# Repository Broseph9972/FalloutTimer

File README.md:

# FalloutTimer

---
The FalloutTimer™ is a simple timer that uses an RTC, A pi Pico, Some buttons, and some cheap 7 segment displays to tell you how much time is left in Hack club fallout!
(Can be used for other things as well)
# Assembly

Assembly is relatively simple, Solder the pico, buttons, caps, and RTC, into the spots they appear on the pcb/zine. look at the zine for info about how to solder the 7-seg display, then flash the firmware by holding down the boot button on the pico while plugging it in. then compile the code and drop the uf2 into the pico's flash. it should reboot and work. Thats really all you need.
--- 
# Usage
Simply set the time via the buttons on the bottom. left button controls days and hrs, left controls mins. seconds are always set to zero for simplicity. if you click the left button it will change hrs, if u hold it down, then it will change days. Thats basically it.
---
## Why?
I decided to make it because i need more time for fallout and it seemed like a simple project i could do to increase my amount of approved hours. also it looks cool as wall deco. ill probably bring it to fallout to show the amount of time left
It displays the time left in fallout with Day,Hour,Minutes,Seconds, similar to the fallout website. also i might get it to check streaks too maybe? <- no wifi so probably not. u would need a pico w aswell.

|Name                       |Price|Link                                                                                                                                                                                                                                                                                                                                                                                                                 |Quantity|Notes                                              |
|---------------------------|-----|---------------------------------------------------------------------------------------------------------------------------------------------------------------------------------------------------------------------------------------------------------------------------------------------------------------------------------------------------------------------------------------------------------------------|--------|---------------------------------------------------|
|7 Segment display          |$2.77|https://www.aliexpress.us/item/2255801097197605.html?algo_exp_id=59cf0bf3-654c-4eec-9474-7ea4b6c6c45e-1&pdp_ext_f=%7B%22order%22%3A%22464%22%2C%22eval%22%3A%221%22%2C%22fromPage%22%3A%22search%22%7D&utparam-url=scene%3Asearch%7Cquery_from%3A%7Cx_object_id%3A4001283512357%7C_p_origin_prod%3A                                                                                                                  |1       |Comes with 8 digits built in. built for 0.56"      |
|Pi Pico                    |$0.99|https://www.aliexpress.us/item/3256806652932348.html?algo_exp_id=9f39b4b5-7e06-4d57-8f12-5c0bc45dbe9d-2&pdp_ext_f=%7B%22order%22%3A%221158%22%2C%22eval%22%3A%221%22%2C%22fromPage%22%3A%22search%22%7D&utparam-url=scene%3Asearch%7Cquery_from%3A%7Cx_object_id%3A1005006839247100%7C_p_origin_prod%3A                                                                                                              |1       |Lots of fakes, shouldnt matter. get usb-c if u want|
|PCB                        |$7.12|JLCPCB.com                                                                                                                                                                                                                                                                                                                                                                                                           |1       |Upload the gerber from the repo.                   |
|DS3231M RTC                |$1.39|https://www.aliexpress.us/item/3256807808551126.html?aem_p4p_detail=202605301909028322147092268240002707967&algo_exp_id=f0b65990-3f51-4963-9e20-ac16821638a2-3&pdp_ext_f=%7B%22order%22%3A%22336%22%2C%22eval%22%3A%221%22%2C%22fromPage%22%3A%22search%22%7D&utparam-url=scene%3Asearch%7Cquery_from%3A%7Cx_object_id%3A1005007994865878%7C_p_origin_prod%3A&search_p4p_id=202605301909028322147092268240002707967_1|1       |so u dont gotta reset the clock everytime          |
|100nF Cap                  |$1.58|https://www.aliexpress.us/item/3256802327709422.html?algo_exp_id=1eb7f3bd-4212-4056-b126-b8978d5f2388-0&pdp_ext_f=%7B%22order%22%3A%22251%22%2C%22eval%22%3A%221%22%2C%22fromPage%22%3A%22search%22%7D&utparam-url=scene%3Asearch%7Cquery_from%3A%7Cx_object_id%3A1005002514024174%7C_p_origin_prod%3A                                                                                                               |1       |Technically optional, but idk                      |
|Pushbuttons                |$0.99|https://www.aliexpress.us/item/2251832687083572.html?algo_exp_id=f1680402-12bf-4261-921e-e1ba355f5f7b-6&pdp_ext_f=%7B%22order%22%3A%22366%22%2C%22eval%22%3A%221%22%2C%22fromPage%22%3A%22search%22%7D&utparam-url=scene%3Asearch%7Cquery_from%3A%7Cx_object_id%3A32873398324%7C_p_origin_prod%3A                                                                                                                    |2       |For input                                          |
|3d printed parts (optional)|$0   |N/A                                                                                                                                                                                                                                                                                                                                                                                                                  |1       |Not needed but just there ig                       |

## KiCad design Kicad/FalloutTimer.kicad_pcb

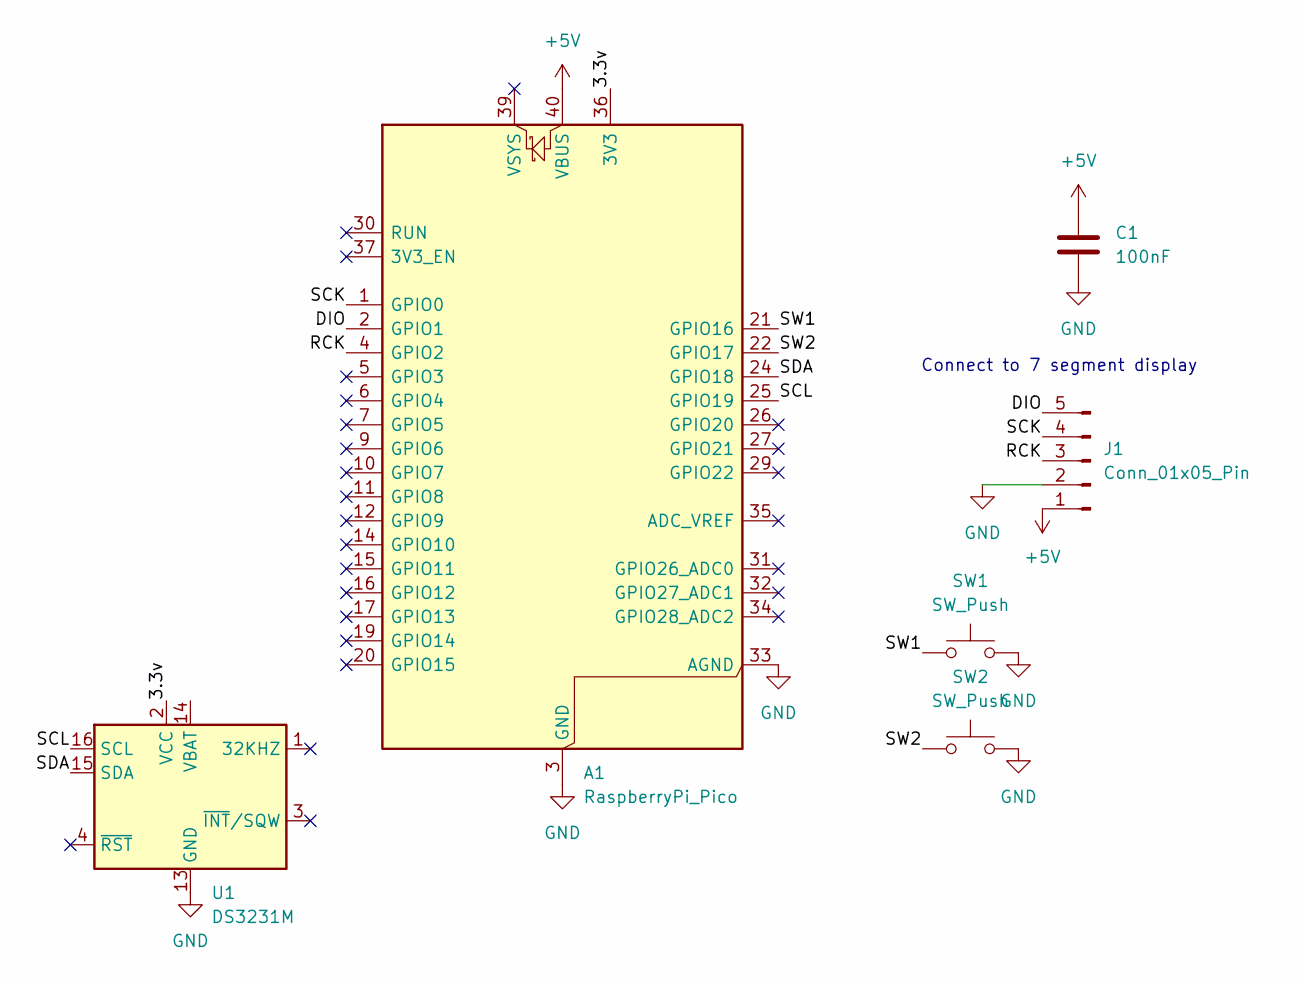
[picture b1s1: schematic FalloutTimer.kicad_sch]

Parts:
A1: RaspberryPi_Pico; RaspberryPi_Pico_Common_Unspecified
C1: 100nF; C_Disc_D5.0mm_W2.5mm_P5.00mm
J1: Conn_01x05_Pin; PinHeader_1x05_P2.54mm_Vertical
SW1, SW2: SW_Push; SW_PUSH_6mm
U1: DS3231M; SOIC-16W_7.5x10.3mm_P1.27mm

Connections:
+5V: A1.40 (VBUS), C1.1, J1.1
/3.3v: A1.36 (3V3), U1.2 (VCC)
/DIO: A1.2 (GPIO1), J1.5
/RCK: A1.4 (GPIO2), J1.3
/SCK: A1.1 (GPIO0), J1.4
/SCL: A1.25 (GPIO19), U1.16 (SCL)
/SDA: A1.24 (GPIO18), U1.15 (SDA)
/SW1: A1.21 (GPIO16), SW1.1
/SW2: A1.22 (GPIO17), SW2.1
GND: A1.3 (GND), A1.8 (GND), A1.13 (GND), A1.18 (GND), A1.23 (GND), A1.28 (GND), A1.33 (AGND), A1.38 (GND), C1.2, J1.2, SW1.2, SW2.2, U1.5 (GND), U1.6 (GND), U1.7 (GND), U1.8 (GND), U1.9 (GND), U1.10 (GND), U1.11 (GND), U1.12 (GND), U1.13 (GND)

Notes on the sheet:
Connect to 7 segment display

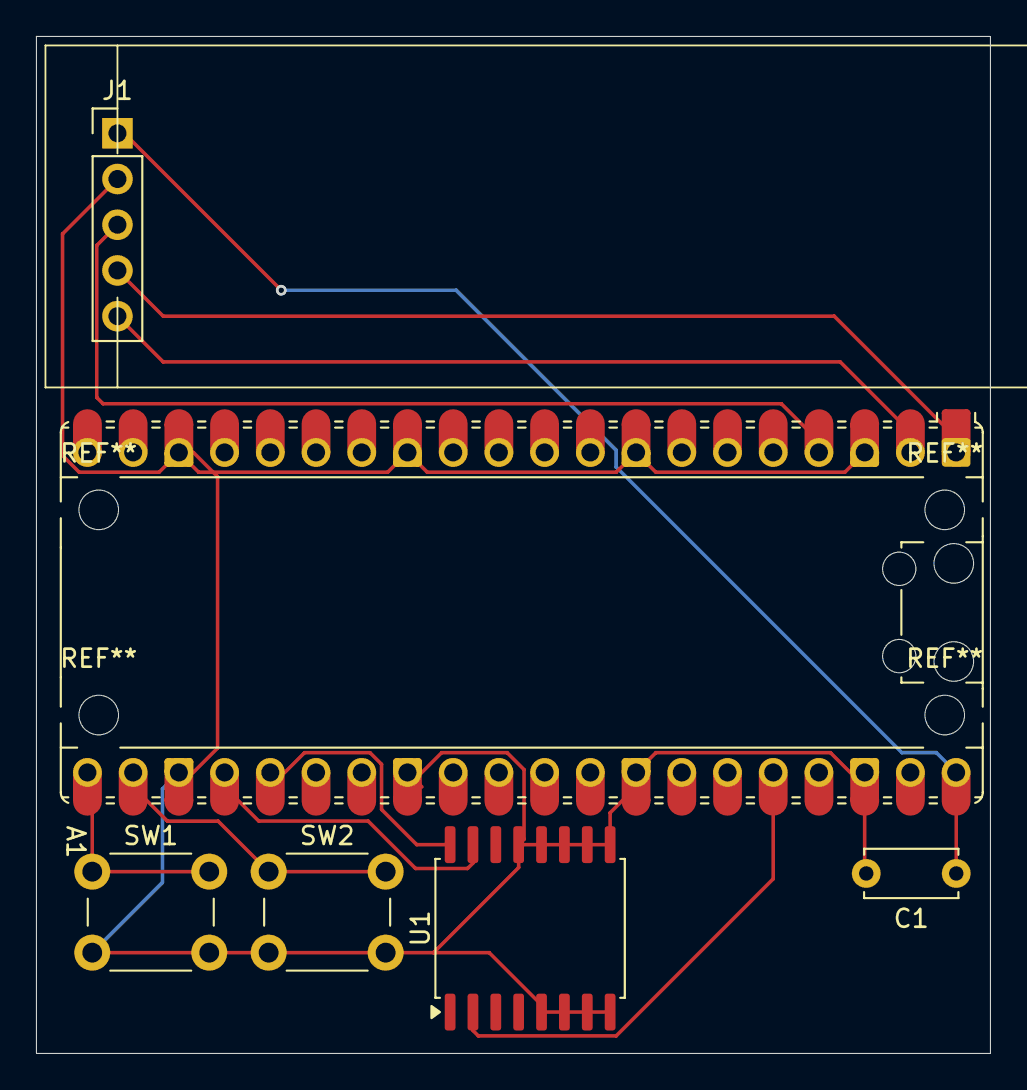
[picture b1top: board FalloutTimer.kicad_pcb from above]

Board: 2 copper layers, 53.0 x 56.5 mm, 6 parts (0 on the bottom side), 10 nets.

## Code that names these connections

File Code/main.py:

import board
import busio
import time
import digitalio
from adafruit_ds3231 import DS3231

# I2C for RTC (SDA=GPIO18, SCL=GPIO19)
i2c = busio.I2C(scl=board.GP19, sda=board.GP18)
rtc = DS3231(i2c)

# 74HC595 shift registers for 8 7-segment displays
# SCK=GPIO0 (clock), DIO=GPIO1 (data), RCK=GPIO2 (latch)
sck = digitalio.DigitalInOut(board.GP0)
sck.direction = digitalio.Direction.OUTPUT

dio = digitalio.DigitalInOut(board.GP1)
dio.direction = digitalio.Direction.OUTPUT

rck = digitalio.DigitalInOut(board.GP2)
rck.direction = digitalio.Direction.OUTPUT

# 7-segment display patterns (common cathode, DP on bit 7)
SEGMENTS = {
    0: 0b00111111,  # 0
    1: 0b00000110,  # 1
    2: 0b01011011,  # 2
    3: 0b01001111,  # 3
    4: 0b01100110,  # 4
    5: 0b01101101,  # 5
    6: 0b01111101,  # 6
    7: 0b00000111,  # 7
    8: 0b01111111,  # 8
    9: 0b01101111,  # 9
    10: 0b00000000  # blank
}

# Pushbuttons (GPIO16 and GPIO17, pulled to GND)
button_left = digitalio.DigitalInOut(board.GP16)
button_left.direction = digitalio.Direction.INPUT
button_left.pull = digitalio.Pull.UP

button_right = digitalio.DigitalInOut(board.GP17)
button_right.direction = digitalio.Direction.INPUT
button_right.pull = digitalio.Pull.UP

# Timer state (in seconds)
time_remaining = 0
setting_mode = False
blink_state = False
blink_time = 0
display_buffer = [10, 10, 10, 10, 10, 10, 10, 10]

def shift_out_byte(byte):
    """Shift out 8 bits to 74HC595"""
    for i in range(8):
        dio.value = (byte >> (7 - i)) & 1
        time.sleep(0.00005)
        sck.value = 1
        time.sleep(0.00005)
        sck.value = 0

def latch():
    """Latch data into output registers"""
    rck.value = 1
    time.sleep(0.0001)
    rck.value = 0

def shift_out_bytes(bytes_list):
    """Shift out multiple bytes (for chaining 74HC595s)"""
    for byte in reversed(bytes_list):  # Reverse for correct bit order
        shift_out_byte(byte)
    latch()

def seconds_to_display(seconds):
    """Convert seconds to day:hour:minute:second format"""
    days = seconds // 86400
    hours = (seconds % 86400) // 3600
    minutes = (seconds % 3600) // 60
    secs = seconds % 60
    return days, hours, minutes, secs

def update_display(days, hours, minutes, secs):
    """Update display buffer with DD:HH:MM:SS"""
    global display_buffer
    display_buffer = [
        days // 10,
        days % 10,
        hours // 10,
        hours % 10,
        minutes // 10,
        minutes % 10,
        secs // 10,
        secs % 10
    ]

def render_display():
    """Send display buffer to 74HC595s"""
    segments = [SEGMENTS.get(d, SEGMENTS[10]) for d in display_buffer]
    shift_out_bytes(segments)

def display_blink():
    """Blink display when timer reaches 0"""
    global blink_state, blink_time
    current_time = time.monotonic()
    if current_time - blink_time > 0.5:
        blink_state = not blink_state
        blink_time = current_time
        if blink_state:
            display_buffer[:] = [10] * 8
        else:
            update_display(0, 0, 0, 0)
    render_display()

def check_both_buttons_held():
    """Check if both buttons are held down"""
    return not button_left.value and not button_right.value

# Main loop
last_second_update = time.monotonic()
left_pressed = False
right_pressed = False
button_held_time = 0

while True:
    current_time = time.monotonic()
    both_held = check_both_buttons_held()
    
    # Enter/exit setting mode
    if both_held and not setting_mode:
        setting_mode = True
        button_held_time = current_time
    elif setting_mode and not both_held:
        setting_mode = False
    
    if setting_mode:
        # In setting mode - adjust time with button presses
        if not button_left.value and not left_pressed:
            # Left button: add hour
            left_pressed = True
            time_remaining = min(time_remaining + 3600, 9999999)
            print(f"Timer: {time_remaining}s (+1h)")
            time.sleep(0.1)
        elif button_left.value:
            left_pressed = False
        
        if not button_right.value and not right_pressed:
            # Right button: add minute (reset seconds), or add day if held
            right_pressed = True
            hold_duration = current_time - button_held_time
            if hold_duration > 1.0:
                # Long hold: add day
                time_remaining = min(time_remaining + 86400, 9999999)
                print(f"Timer: {time_remaining}s (+1d)")
            else:
                # Short press: add minute, reset seconds
                time_remaining = (time_remaining // 60 + 1) * 60
                time_remaining = min(time_remaining, 9999999)
                print(f"Timer: {time_remaining}s (+1m)")
            time.sleep(0.1)
        elif button_right.value:
            right_pressed = False
        
        # Display time being set
        days, hours, minutes, secs = seconds_to_display(time_remaining)
        update_display(days, hours, minutes, secs)
        render_display()
    
    else:
        # Normal countdown mode
        if current_time - last_second_update >= 1.0:
            if time_remaining > 0:
                time_remaining -= 1
            last_second_update = current_time
        
        # Display countdown or blink
        if time_remaining > 0:
            days, hours, minutes, secs = seconds_to_display(time_remaining)
            update_display(days, hours, minutes, secs)
            render_display()
        else:
            display_blink()

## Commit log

2026-05-28 some stuffs
2026-05-29 PCB and Schema mostly done
2026-05-30 added an outline for the display on the pcb
2026-05-31 ummm idk
2026-05-31 Finsihed PCB.
    asdasd
2026-05-31 Added the kicad gitignore so i dont get .history changes.
2026-05-31 gerberessssss
2026-05-31 Janky hopefully precise enough screw holes
    i basically just put them where the pico holes are.
2026-05-31 new .step
2026-06-01 shitty code
2026-06-04 added zine pics
    exported from figma
2026-06-04 New bom
2026-06-04 added onshape link
2026-06-04 onshape link finally
2026-06-04 Added Case
2026-06-15 New screenshot
2026-06-19 no more onshape
2026-06-19 Add M2 screws and bolts to BOM CSV
2026-06-19 Good Cad
